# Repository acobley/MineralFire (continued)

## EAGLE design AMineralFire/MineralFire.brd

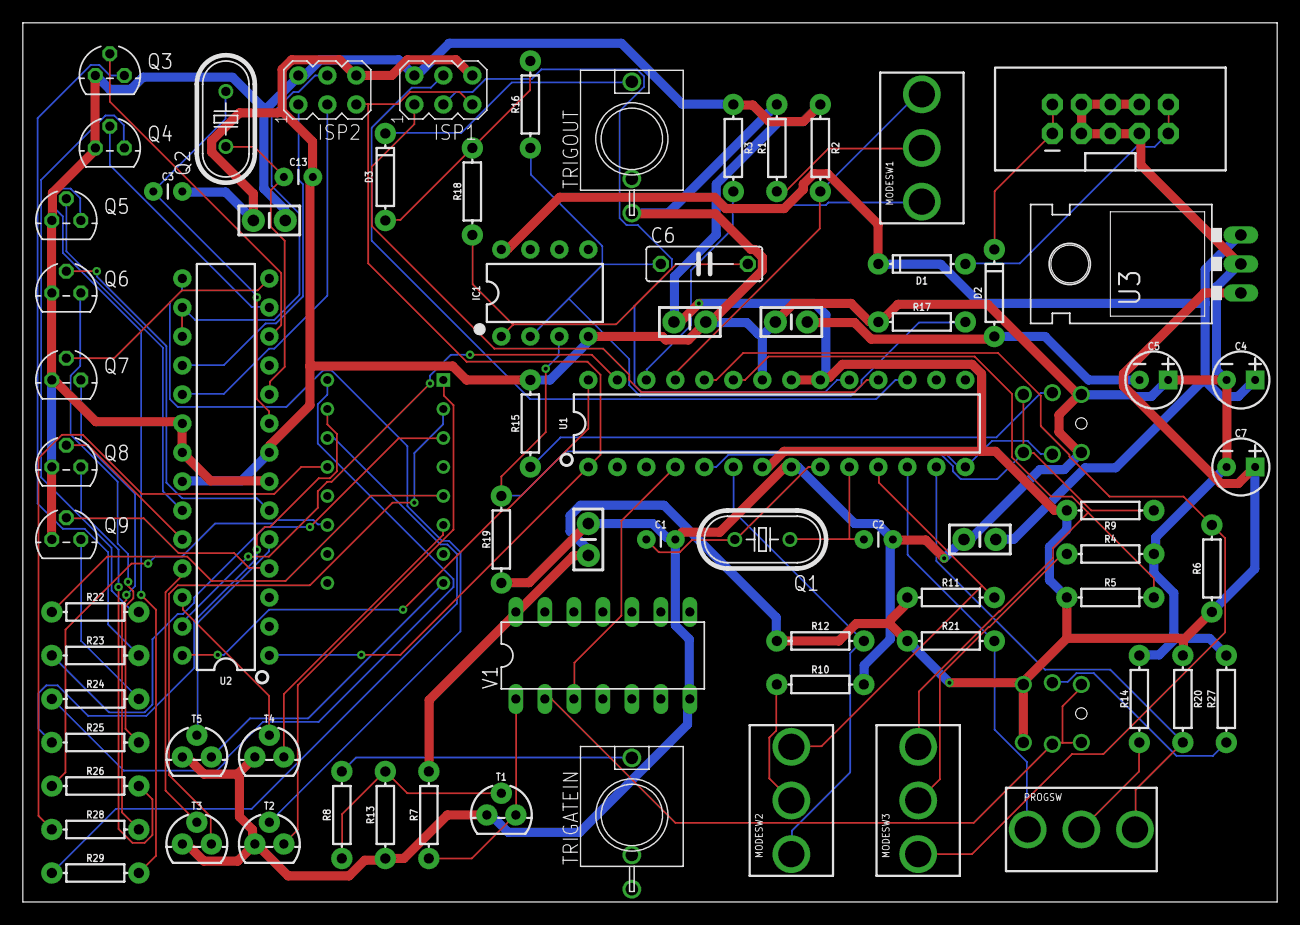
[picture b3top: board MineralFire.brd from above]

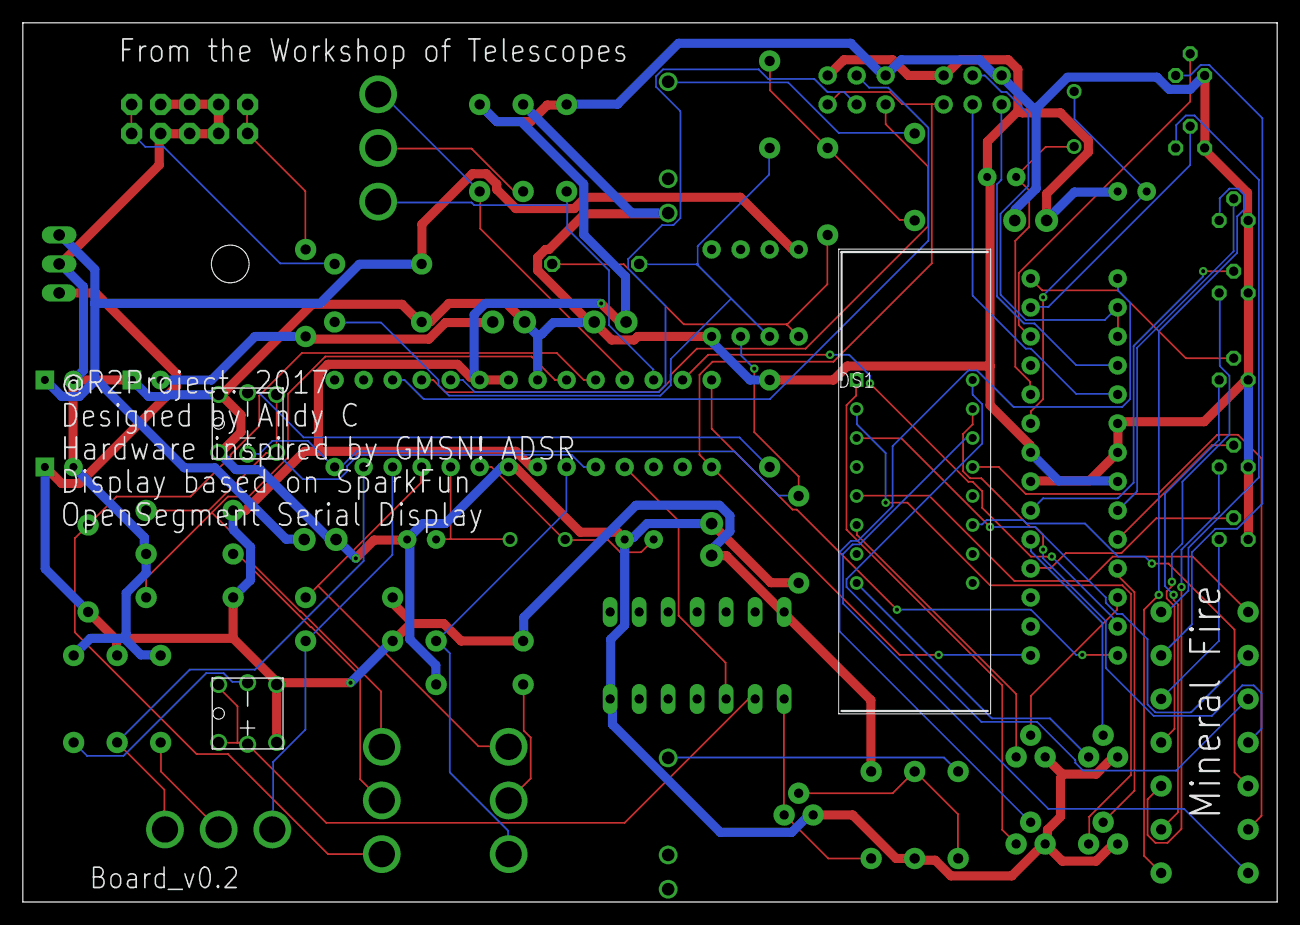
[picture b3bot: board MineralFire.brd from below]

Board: 2 copper layers, 109.9 x 77.0 mm, 76 parts (3 on the bottom side), 73 nets.

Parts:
BUT, BUT1: PB6149L-5; PB6149L
C1, C2, C3, C13: 22pF; CAP-PTH-2.54
C4, C5, C7: 10uF; CPOL-RADIAL-2.5MM-5MM
C6: 100pf; C075-032X103
C8, C9, C10, C11, C12: 0.1uF; CAP-PTH-SMALL-KIT
D1, D2, D3: 200mA/100V/1V; DIODE-1N4148
DS1: TDCG1060M; DIPS1016W50P254L4020H700Q16N
IC1: LM358; DIP08
ISP1, ISP2: AVRISP-6; AVRISP
MODESW1, MODESW2, MODESW3: TOGGLE_ON_OFF_ON
POWER: M05X2SHD; 2X5-SHROUDED
PROGSW: TOGGLE_ON_OFF_ON
Q1, Q2: 20MHz; HC49U70
Q3, Q4, Q5, Q6, Q7, Q8, Q9: 2N3906; TO92
R1, R4, R10, R14, R18: 1k; AXIAL-0.3
R2, R3, R5, R6, R8, R11, R12, R16, R17, R19, R20, R21: 100k; AXIAL-0.3
R7, R9: 10k; AXIAL-0.3
R13: 1M; AXIAL-0.3
R15: 330; AXIAL-0.3
R22, R23, R24, R25, R26, R28, R29: 100; AXIAL-0.3EZ
R27: 150; AXIAL-0.3
T1, T2, T3, T4, T5: 200mA/40V; TO-92
TRIGATEIN: S_JACK
TRIGOUT: S_JACK
U1, U2: 328P; DIP28
U3: 7805; TO-220-ALT
V1: 7432N; DIL14

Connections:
+5V: BUT1.1, BUT1.2, C7.1, C10.1, C11.1, C12.1, ISP1.2, ISP2.2, Q3.3, Q4.3, Q5.3, Q6.3, Q7.3, Q8.3, Q9.3, R2.P$1, R3.P$1, R5.P$1, R6.P$1, R7.P$2, R9.P$2, R11.P$1, R12.P$1, R20.P$1, R21.P$1, U1.7, U1.20, U1.21, U2.7, U2.20, U2.21, U3.IN, V1.14
+12V: C4.1, C8.1, D1.C, IC1.8, U3.OUT
-12V: C5.2, C9.2, D2.A
AN-A: DS1.14, R29.P$1
AN-B: DS1.16, R24.P$1
AN-C: DS1.13, R28.P$1
AN-D: DS1.3, R23.P$1
AN-E: DS1.5, R22.P$1
AN-F: DS1.11, R26.P$1
AN-G: DS1.15, R25.P$1
B_TRIG: BUT.1, BUT.2, R9.P$1, U1.5
C-DIG1: T2.2, U2.15
C-DIG2: T3.2, U2.25
C-DIG3: T4.2, U2.26
C-DIG4: T5.2, U2.5
C-SEGA: Q5.2, U2.23
C-SEGB: Q9.2, U2.4
C-SEGC: Q7.2, U2.14
C-SEGD: Q3.2, U2.12
C-SEGE: Q4.2, U2.13
C-SEGF: Q8.2, U2.24
C-SEGG: Q6.2, U2.6
D1: DS1.1, T2.3
D2: DS1.2, T3.3
D3: DS1.6, T4.3
D4: DS1.8, T5.3
GND: BUT.3, BUT.4, C1.2, C2.2, C3.2, C4.2, C5.1, C7.2, C8.2, C9.1, C10.2, C11.2, C12.2, C13.2, IC1.4, ISP1.6, ISP2.6, POWER.3, POWER.4, POWER.5, POWER.6, POWER.7, POWER.8, R1.P$2, R4.P$2, R10.P$2, R13.P$1, R14.P$2, R15.P$2, R17.P$1, R19.P$1, R27.P$2, T1.1, T2.1, T3.1, T4.1, T5.1, TRIGATEIN.GND, TRIGOUT.GND, U1.8, U1.22, U2.8, U2.22, U3.GND, V1.7
LBUTTON: BUT1.3, BUT1.4, BUT1.A, V1.2
LTRIG: R7.P$1, T1.3, V1.1
MISO: ISP1.1, U1.18
MISO2: ISP2.1, U2.18
MOSI: ISP1.4, U1.17
MOSI2: ISP2.4, U2.16, U2.17
unnamed: C1.1, Q1.2, U1.9
unnamed: C2.1, Q1.1, U1.10
unnamed: MODESW1.2, R1.P$1
unnamed: MODESW3.2, R4.P$1
unnamed: Q4.1, R22.P$2
unnamed: PROGSW.2, R14.P$1
unnamed: C3.1, Q2.2, U2.9
unnamed: C13.1, Q2.1, U2.10
unnamed: D1.A, POWER.9, POWER.10
unnamed: D2.C, POWER.1, POWER.2
unnamed: Q3.1, R23.P$2
unnamed: MODESW2.2, R10.P$1
unnamed: Q9.1, R24.P$2
unnamed: Q8.1, R26.P$2
unnamed: R8.P$1, R13.P$2, T1.2
unnamed: Q7.1, R28.P$2
unnamed: Q6.1, R25.P$2
unnamed: R8.P$2, TRIGATEIN.TIP
unnamed: BUT1.K, R27.P$1
unnamed: Q5.1, R29.P$2
unnamed: BUT.K, R15.P$1
unnamed: C6.1, IC1.2, R16.P$1, R17.P$2
unnamed: C6.2, IC1.1, R18.P$1
unnamed: D3.A, R16.P$2, R18.P$2
unnamed: D3.C, TRIGOUT.TIP
RST: ISP1.5, ISP2.5, U1.1, U2.1
SCK: ISP1.3, U1.19
SCK2: ISP2.3, U2.19
SCL: U1.28, U2.28
SDA: U1.27, U2.27
T1: MODESW2.3, R11.P$2, U1.11
T2: MODESW2.1, R12.P$2, U1.6
T3: MODESW1.3, R2.P$2, U1.25
T4: MODESW1.1, R3.P$2, U1.26
T5: MODESW3.3, R5.P$2, U1.23
T6: MODESW3.1, R6.P$2, U1.24
T7: PROGSW.1, R21.P$2, U1.12
T8: PROGSW.3, R20.P$2, U1.13
TRIG: U1.4, V1.3
TRIGO: BUT.A, IC1.3, R19.P$2, U1.14

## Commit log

2016-02-14 removed serial output
2016-02-14 Fixed counter count error
2017-02-06 Tryin interupt
2017-02-08 built in led flash
2017-02-08 New Branch
2017-02-08 removed dead code
2017-02-08 counter set
2017-02-08 getting there
2017-02-10 firstworking version
2017-02-10 added barcount, not tested
2017-02-17 Variable length bars
2017-02-19 LED support
2017-02-25 dimed LEd, fixed count issue
2017-03-05 added running switch
2017-03-05 Updated comments
2017-06-28 different counter
2017-06-29 array count works
2017-07-01 New Switches for patterns
2017-07-03 added Eagle files
2017-07-05 Working on moving SMT to tru-the hole
2017-07-05 First Attempt at layout
2017-07-05 Change start/stop button to interrupt
2017-07-05 Small change to Readme
2017-07-08 ground in fill
2017-07-08 debounce switch
2017-07-08 New Layout
2017-07-08 Added switch on analogue in for mode
2017-07-09 changed file name
2017-07-09 updated design files
2017-07-09 removed Volca_Pulse.ino
2017-07-09 removed .ino~ file
2017-07-09 Added README
2017-07-12 added name
2017-07-13 added LED in switch
2017-07-14 Added AND gate on trigger
2017-07-17 LED in count switch
2017-07-19 Board too big
2017-07-19 Shrunk board by 5mm
2017-07-19 changing Pins to new layout
2017-07-20 setup new branch for experiment
2017-07-20 minor change
2017-07-20 Added correct gate and pulse length
2017-07-20 Starting to add support of simple division
2017-07-22 corrected Pulse edge
2017-07-22 added 3d Printed Panel
2017-07-23 added test programs
2017-07-23 Code complete for v0.1
2017-07-26 Larger Board
2017-07-26 adding Display
2017-07-26 Updated Panel
2017-07-28 Changed to 8 stage
2017-07-30 Vishray 7 segment display
2017-07-30 first layout
2017-07-31 On Order
2017-08-01 moving to SMD
2017-08-01 Continuing move to SMD
2017-08-02 Moving atmega to smd
2017-08-02 Fixed r22 etc
2017-08-02 Fixed up reset
2017-08-03 first SMD
2017-08-03 added BOM and Gerber
2017-08-04 routing
2017-08-05 Fixed switches, added tempo
2017-08-05 added smd bom
2017-08-05 Added simple tempo calc
2017-08-07 Fixed RST on ISP2 and regulator was wrong way round
2017-08-10 added test for seven segment display
2017-08-11 Code for seven segment test
2017-08-12 Added display code and test IC2
2017-08-20 changed push button
2017-08-20 updated test code
2017-08-21 updated to and gate
2017-08-23 added diode to switch
2017-08-26 new input circuit
2017-08-26 new layout with input gate on left
2017-08-27 new routing:
2017-09-05 Added Gate Out test
2017-09-09 added more test code
2017-09-09 updated flash
2017-09-10 added tests and Div code from V0.1
2017-09-10 Input circuit test added
2017-09-10 updated input circuit switch
2017-09-11 Added dispay code
2017-09-11 Minor comment to test led
2017-09-14 fixed some inputs
2017-09-16 Fixed display code
2017-09-16 Turned brightness down
2017-09-17 Update display comms
2017-09-17 update main code to transmit in new way
2017-10-16 tidying
2017-10-29 minor changes
2017-10-30 Added interupt on/off
2017-10-30 cli to TestIC2.ino
2017-10-31 updated to I2C
2018-03-22 Started SMD board
2018-03-22 Updated to almost all SMD
2018-03-22 changes to 0.3-smd
2018-03-23 0.3-smd nor fully smd
2018-03-23 Added pull up resistors on I2C comms
2018-03-27 Backlink to CADLAB.io has been added.
2018-04-02 Layout chnaged
2018-04-04 changed nothing
2018-04-04 taken boadr down to 100mm
2018-04-04 0.3 smd panel added
2018-08-07 added in progress
2018-08-08 Updated design to use rotary encoder
2018-08-08 routing on board
2018-08-19 Fixed routing errors
2018-08-19 added OLED board
2018-08-19 Towards OLED
2018-08-19 removed previous versions from this branch
2018-08-19 trying connector for oled
2018-10-02 upadted
